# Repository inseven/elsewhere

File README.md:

# Elsewhere

Livestream picture frame

## Parts

| **Part**                                  | **Link**                                                     | Quantity | **Unit Price**            | **Price**   |
| ----------------------------------------- | ------------------------------------------------------------ | -------- | ------------------------- | ----------- |
| **Raspberry Pi Zero 2 W**                 | [Adafruit](https://www.adafruit.com/product/5291) | 1        | $15.00                   | $15.00     |
| **Pimoroni HDMI 10" IPS LCD Screen Kit**  | [Adafruit](https://www.adafruit.com/product/4337)            | 1        | $139.95                   | $139.95     |
| HDMI Ribbon Cable, 30 cm                  | [Adafruit](https://www.adafruit.com/product/3562)            | 1        | $2.75                     | $2.75       |
| HDMI Plug Adapter                         | [Adafruit](https://www.adafruit.com/product/3548)            | 1        | $6.50                     | $6.50       |
| Mini HDMI Plug Adapter                    | [Adafruit](https://www.adafruit.com/product/3552)            | 1        | $6.50                     | $6.50       |
| **ATXRaspi R3**                           | [LowPowerLab](https://lowpowerlab.com/shop/product/91)       | 1        | $17.95                    | $17.95      |
| Jumper Wire | [LowPowerLab](https://lowpowerlab.com/shop/product/154) | 4 | $0.74 ($2.95 for 4) | $2.95 |
| D-Ring Picture Hanger, M4                 |                                                              | 2        |                           |             |
| USB-C Panel Mount                         | [eBay](https://www.ebay.com/itm/143134180140)                | 1        | $6.29                     | $6.29       |
| USB-C to Micro USB Adapter                | [Amazon](https://www.amazon.com/gp/product/B07GH5KJH2/)      | 1        | $6.99                     | $6.99       |
| Micro USB Splitter Cable                  | [Amazon](https://www.amazon.com/gp/product/B017OPOG58/)      | 1        | $6.79                     | $6.79       |
| microSD Card, 32GB                        | [Amazon](https://www.amazon.com/SAMSUNG-Select-microSDXC-Adapter-MB-ME128HA/dp/B06XWN9Q99) | 1        | $7.99                     | $7.99       |
| Female to Female Dupont Wire, 30cm | [Amazon](https://www.amazon.com/dp/B07GD1W1VL) | 6 | $0.08 ($8.99 for 120) | $0.48 |
| M3 Standoff, 10mm                         | [McMaster-Carr](https://www.mcmaster.com/94868A166/)         | 8        | $1.24                     | $9.92       |
| 4-40 Socket Head Screw, Low-Profile, 1/4" | [McMaster-Carr](https://www.mcmaster.com/93615A110/)         | 2        | $1.55 (Pack of 10)        | $3.10       |
| M3 Socket Head Screw, Low-Profile, 12mm   | [McMaster-Carr](https://www.mcmaster.com/92855A313/)         | 8        | $0.11 (Pack of 25)        | $0.22       |
| M3 Socket Head Screw, Low-Profile, 6mm    | [McMaster-Carr](https://www.mcmaster.com/92855A307/)         | 8        | $0.30 (Pack of 25)        | $0.60       |
| M2.5 Socket Head Screw, 6mm               | [McMaster-Carr](https://www.mcmaster.com/91292A010/)         | 18      | $0.06 ($6.00 for 100) | $1.08    |
| M2.5 Socket Head Screw, 4mm | [McMaster-Carr](https://www.mcmaster.com/91292A015/) | 18 | $0.30 ($7.43 for 25) | $5.40 |
| M2.5 Socket Head Screw, 10mm | [McMaster-Carr](https://www.mcmaster.com/91292A014/) | 2 | $0.07 ($6.54 for 100) | $0.14 |
| M2.5 Nut | [McMaster-Carr](https://www.mcmaster.com/91828A113/) | 2 | $0.08 ($7.18 for 100) | $0.16 |
| M2.5 Washer, 0.5mm | [McMaster-Carr](https://www.mcmaster.com/98689A111/) | 6 | $0.03 ($2.57 for 100) | $0.18 |
| M4 Socket Head Screw, Low-Profile, Partially Threaded, 10mm | [McMaster-Carr](https://www.mcmaster.com/96970A111/) | 2 | $1.48 | $2.96 |
| M4 Washer, 0.8mm | [McMaster-Carr](https://www.mcmaster.com/93475A230/) | 2 | $0.04 ($3.14 for 100) | $0.08 |
| M4 Locknut | [McMaster-Carr](https://www.mcmaster.com/93625A150/) | 2 | $0.08 ($7.67 for 100) | $0.16 |
| M2.5 Standoff, 6mm                        | [Digi-Key](https://www.digikey.com/en/products/detail/970060154/732-12827-ND/9488531) | 18      | $0.34 ($16.95 for 50) | $6.12   |
| **Laser-Cut Parts** | [Ponoko](https://ponoko.com) |  |  | $118.99 |
| **Controller Board** | [Oshpark](https://oshpark.com/shared_projects/Cnb1DUgJ) | 1 | $3.49 ($10.45 for 3) | $3.49 |
| Micro SD to Micro SD Extension Cable, 25cm | [AliExpress](https://www.aliexpress.com/item/4001154489373.html) | 1 | $3.00 | $3.00 |
|                                           |                                                              |          |                           | **$375.74** |

## Wiring

## Software Installation

1. Install Raspberry Pi OS Lite (Bullseye).

2. Add the package repository to `/etc/apt/sources.list`:

   ```bash
   deb [trusted=yes] http://packages.inseven.co.uk/raspbian/ ./
   ```

3. Update the `dtoverlay` property in `/boot/config.txt` to:

   ```ini
   dtoverlay=vc4-fkms-v3d
   ```

   (See https://forums.raspberrypi.com/viewtopic.php?t=324835.)
   
4. Add `fbcon=map:2 disable_splash=1 ` to `/boot/cmdline.txt`.

   These changes are as follows:

   - `fbcon=map:2` – Redirects the console during boot to ensure it doesn't appear on the HDMI display.
   - `disable_splash=1` – Disable the boot splash screen.

5. Disable the Serial Port and SPI:

   ```bash
   sudo raspi-config
   ```

   - Disable Serial Port
     - Interface Options
     - Serial Port
     - Login Shell: No
     - Serial Port Hardware: No
   - Disable SPI
     - Interface Options
     - SPI
     - Enabled: No

6. Reboot:

   ```bash
   sudo reboot
   ```

7. Update and upgrade Raspbian, and install Elsewhere:

   ```bash
   sudo apt update
   sudo apt upgrade --yes
   sudo apt install elsewhere --yes
   ```

8. Assuming everything has gone to plan, Elsewhere should now be running.

#### Unattended Upgrades

1. Enable all [unattended upgrades](https://wiki.debian.org/UnattendedUpgrades) by uncommenting the following lines in `/etc/apt/apt.conf.d/50unattended-upgrades`:

   ```
   Unattended-Upgrade::Origins-Pattern {
           // ...
           "origin=Debian,codename=${distro_codename}-updates";
           "origin=Debian,codename=${distro_codename}-proposed-updates";
           // ..
   }
   ```

2. Reboot:

   ```bash
   sudo reboot
   ```

## Troubleshooting

### Device takes too long to shutdown and ATXRaspi doesn't cut power

- Re-enable the console by removing `fbcon=map:2` from `/boot/cmdline.txt`.
- Check the the shutdown logs; are any services taking a long time to stop?

### Tailscale doesn't takes too long to stop

Customise the Tailscale service to shorten the shutdown timeout:

- Override the service:

  ```bash
  sudo systemctl edit tailscaled.service
  ```

- Add the following section:

  ```
  [Service]
  TimeoutSec=5
  ```

## Builds

Elsewhere is an iterative project, meaning I've put together a number of prototypes along the way. The most recent one still has the 4:3 aspect ratio, and has been happily showing us views from the ISS for the last few months.

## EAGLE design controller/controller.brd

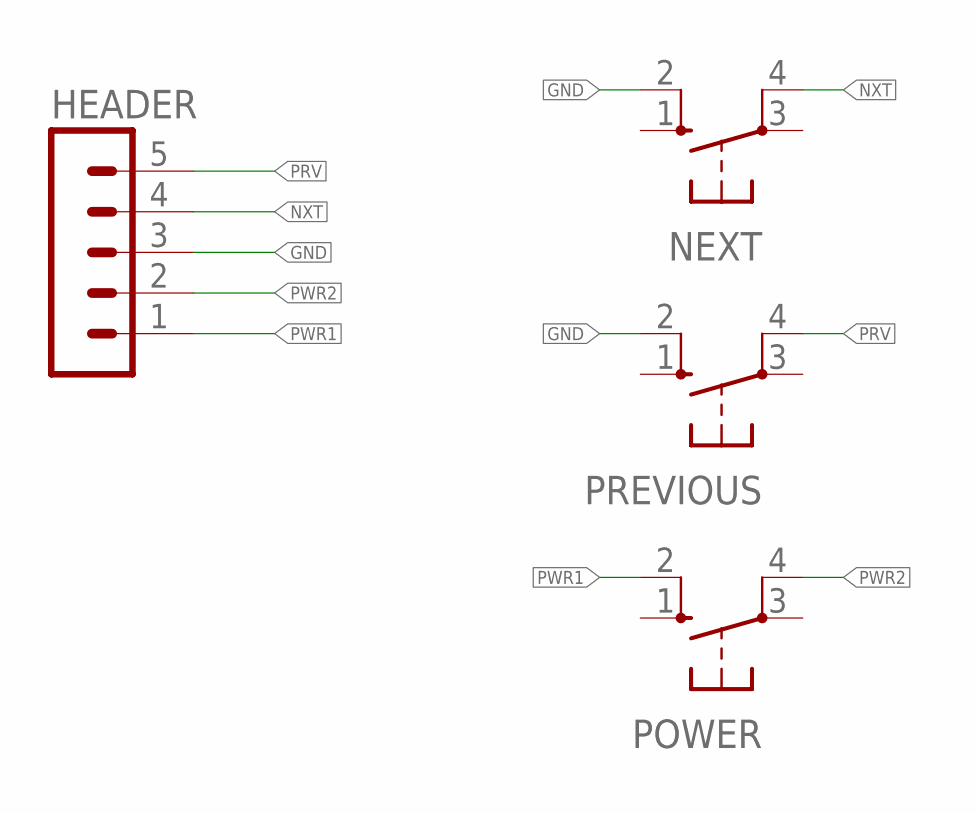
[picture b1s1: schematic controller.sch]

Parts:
HEADER: MA05-1
NEXT: 10-XX; B3F-10XX
POWER: 10-XX; B3F-10XX
PREVIOUS: 10-XX; B3F-10XX

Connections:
GND: HEADER.3, NEXT.2 (S1), PREVIOUS.2 (S1)
NXT: HEADER.4, NEXT.4 (P1)
PRV: HEADER.5, PREVIOUS.4 (P1)
PWR1: HEADER.1, POWER.2 (S1)
PWR2: HEADER.2, POWER.4 (P1)

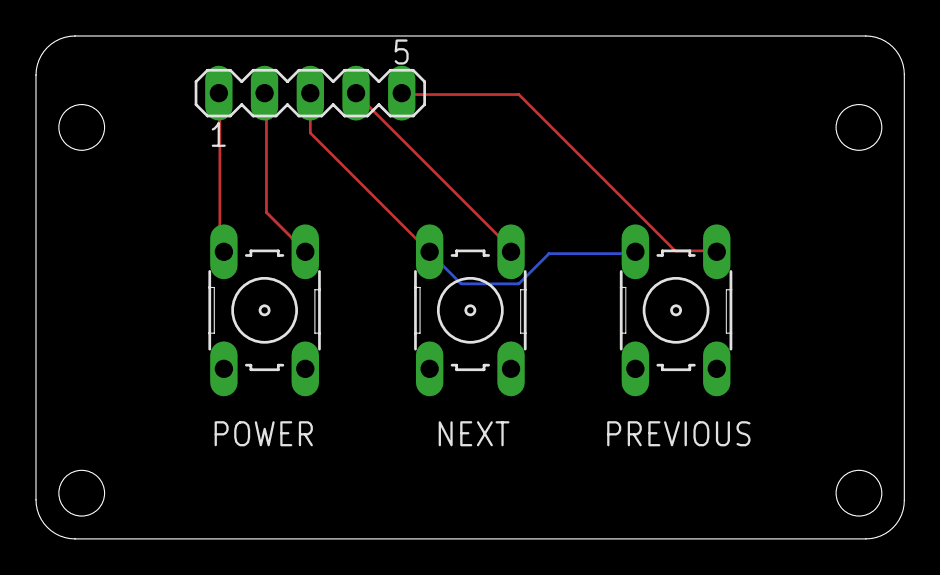
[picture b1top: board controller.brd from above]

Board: 2 copper layers, 48.2 x 27.9 mm, 4 parts (0 on the bottom side), 5 nets.

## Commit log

2018-09-07 Add template for fullscreen video.
2018-09-07 Render the template for each URL and display this.
2018-09-07 Prevent Chromium from restoring state.
2018-09-07 Use a temporary file.
2018-09-07 Black background.
2019-06-05 Add the model details.
2020-02-13 Add the manual for LP097QW1-SPC1.
2020-02-13 Move the schematics around, and add an export of just the front schematic.
2020-02-13 Add the SVG of the display schematics.
2020-04-29 Add prototype sketch.
2020-06-26 Update the elsewhere script to the new playback strategy.
2020-06-26 Update the name.
2020-06-26 Remove the unnecessary template.
2020-06-26 Support changing channels.
2020-06-27 Add a script for configuring elsewhere and update the readme accordingly.
2020-06-27 Experimental support for respawning the player if it crashes.
2020-06-28 Support changing channels with the threaded player.
2020-06-28 Sudo for reboot.
2020-06-30 Add CAD model.
2020-07-08 Replace the Tokyo stream.
2020-07-10 Update the CAD files.
2020-08-03 Support URL-based stream configuration.
2020-08-03 Update the setup script to configure simple logging.
2020-08-03 Ignore comments in the URL list.
2020-08-03 Ensure the process is launched using bash to allow us to use pipes.
2020-08-17 Support local files.
2020-08-17 Ignore urls.txt.
2020-08-18 Support skipping GPIO for control buttons and use the Pimoroni Inky pHAT as a display for stream titles.
2020-08-22 Add a preview.
2020-08-22 Add panel schematic
2020-08-22 Add a model
2020-08-22 More dependencies
2020-08-24 Add Raspberry Pi Zero schematic.
2020-08-25 Add the new manufacture exports.
2020-08-25 Rename placeholder screenshot.
2020-08-25 Move the prototype sketches into the models folder.
2020-08-25 Update the BOM
2020-08-25 Add the HDMI cable
2020-08-25 Update the render.
2020-08-25 Add a web server for controlling the device.
2020-08-25 Add a simple web app, and consolidate the player controls.
2020-08-29 Use the command line vlc client, and remove the eInk output for the time being.
2020-08-30 Adding the splash screen.
2020-08-30 Improving the layout of the controls slightly.
2020-08-30 Don't show the title when starting the stream.
2020-08-30 Add the Illustrator file for the splash screen.
2020-09-10 Add the first-cut service files.
2020-09-10 Lowercase buttons.
2020-12-30 Remove the legacy setup code.
2020-12-30 Titlecase.
2020-12-30 More titlecase.
2021-11-13 Add updated cut files with wider aspect ratio and many improvements
    - control mounts
    - improved hook mounting
    - larger USB-C cutout
    - SD card access
    - cleaner sides (fewer vents)
    - hidden joint between side panels
2021-11-16 Don't round the corners.
2021-11-17 Update the parts listing.
2021-11-17 Add the USB-C mounting screws.
2021-11-17 More screws, and total price.
2021-11-17 Add the ATXRaspi.
2021-11-17 Add screw.
2021-11-19 Add the microSD card to the BOM.
2021-11-24 Add the ATX-Raspi repository as a submodule.
2021-11-24 Add the ATXRaspi schematic from the website.
2021-11-26 Improve the setup documentation.
2021-11-26 Add PCB mounting standoffs and screws.
2021-11-27 Add an updated render.
2021-11-27 Brief comment about the most recent prototype.
2021-11-27 Gorup all the Adafruit components together.
2021-11-27 Cleaning up the multi-pack description.
2021-11-27 Add the v4 manufacture DXF files.
2021-11-27 Add an updated bottom side for the v3 build with a cutout for the power microswitch
2021-11-27 Add another stnadard part.
2021-11-27 Add the laser cut parts to the BoM.
2021-12-06 Add a simple script for showing the splash screen.
2021-12-06 Fix the path to the splash image.
2021-12-06 Add the Python requirements and a wrapper script to update them on first run
2021-12-06 Hard-code the path to streamlink.
2021-12-06 Add a package dependency file.
2021-12-06 Remove the legacy setup.py
2021-12-06 Remove the prototype eInk script.
2021-12-06 Add python-setuptools to the dependencies.
2021-12-06 Add the unattended updates packages.
2021-12-06 Some unattended updates setup.
2021-12-06 Remove legacy services.
2021-12-06 Update the README with further instructions for Bullseye.
2021-12-06 Fleshing out the UI a little.
2021-12-06 Updating the installation instructions and the install script.
2021-12-06 Add splash for shutting down.
2021-12-13 Add a small PCB with buttons for power and controlling the channels
2021-12-13 Link the controller PCB with Fusion.
2021-12-14 Add the latest manufacture files.
2021-12-18 Update the PCB mounting standoffs and screws.
2021-12-27 fix: Don't update the Python dependencies on every run
2021-12-27 fix: Support ATXRaspi power manaagement and add a splash screen
2021-12-27 fix: Use title case for the application name in the web frontend
2021-12-27 fix: Use Inter as the splash screen font
2021-12-27 chore: Remove the legacy Illustrator splash screens
2021-12-27 refactor: Move the splash service into the 'splash' directory
2021-12-27 fix: Don't use cron for running Elsewhere
2021-12-27 feat: Add a service for running the main Elsewhere script
2021-12-27 feat: Add the ATXRaspi monitor
2021-12-27 chore: Add a license to atx-monitor.py
2021-12-27 fix: Update the install script
2021-12-27 ci: Add empty GitHub Actions build
2021-12-27 ci: Correct the whitespace in the workflow (thanks Emacs)
2021-12-27 ci: Correct the target runner
2021-12-27 ci: Call the build script
2021-12-27 ci: Use a relative path to the build script
2021-12-27 ci: Build a dummy package
2021-12-27 feat: Install the splash screen service using the new debian package
2021-12-27 feat: Install the elsewhere service using the debian package
2021-12-27 fix: Remove the legacy package install step from `install.sh`
2021-12-27 ci: Archive the Debian package
2021-12-27 feat: Move the ATXRaspi monitor into the debian package
2021-12-27 feat: Move the elsewhere script into the debian package
2021-12-27 refactor: Remove the `install` command from atx-monitor
2021-12-27 ci: Add changes as a submodule
2021-12-27 docs: Add a build status badge
2021-12-27 fix: Include the Python dependencies in the debian package
2021-12-27 refactor: Move `requirements.txt` into the package directory
2021-12-27 fix: Python dependencies no longer need to be installed separately
2021-12-27 refactor: Move `install.sh` into the `scripts` directory
2021-12-27 feat: Add the version number to the splash screen
2021-12-27 fix: Show the version number in smaller font on the spash screen
2021-12-27 refactor: Move the build script into the scripts directory
2021-12-27 docs: Add a top-level license
2021-12-28 feat: Auto-generate version numbers using the `changes` script
2021-12-28 ci: Version number generation requires a full checkout
2021-12-28 ci: Correct the YAML whitespace (thanks Emacs)
2021-12-28 ci: Clear the Python dependencies on each re-install
2021-12-28 ci: Include the version number in the debian package filename
2021-12-28 ci: Rename the artifacts to `build`
2021-12-28 ci: Add an optional install step to the build script
2021-12-28 ci: Automatically create GitHub releases
2021-12-28 ci: Fix Emacs whitespace YAML errors
2021-12-28 fix: Update the package description
2021-12-29 fix: Set the Debian package build number
2021-12-29 fix: Only show the version number during startup
2021-12-30 feat: Generate a splash screen for use when restarting
2021-12-30 ci: Automatically update the package repository on main builds
2021-12-30 ci: Test package rebuild triggers
2021-12-30 fix: Artificially generated empty update to check the build process
2021-12-31 feat: Sign the debian packages
2021-12-31 ci: Remove control characters from the build workflow
2021-12-31 ci: Ensure `~/.gnupg` exists
2021-12-31 ci: Don't attempt to cleanup the GPG keys before they've been added
2021-12-31 docs: Update the documentation to use the new debian package
2022-01-02 chore: Add copyright header to the source files
2022-01-04 feat: Show stream titles
2022-01-04 fix: Add a dependency on ImageMagick
2022-01-05 fix: Correct the title for the Shinjuku stream
2022-01-05 feat: Add Shibuya Crossing stream
2022-01-08 docs: Add some troubleshooting documentation
2022-01-16 Update for the Raspberry Pi Zero 2 W.
2022-01-16 Remove two now-unused components
2022-01-17 Update the total price to account for the previously removed items
2022-01-17 Add the Elsewhere controller board to the BoM
2022-01-17 Add the Micro SD extension cable to the BoM
2022-01-17 Add the v6 DXF files
2022-01-17 Add the M4 mounting hardware from McMaster-Carr
2022-01-17 Add the SD card mounting hardware and the wires to the BoM
2022-01-17 Add models.
2022-01-21 feat: Add Brownville stream
2022-03-24 docs: Add a photo showing the internal inter-board wiring
2022-07-19 docs: Update the project description
2022-07-19 docs: Correct the updated project description
2022-12-19 docs: Update the description
2023-01-23 ci: Update `changes` to address new Pipenv requirements
2023-01-23 Don't install the GitHub CLI as part of the build
2023-01-23 ci: Update `changes` to address new Pipenv requirements (#52)
2023-01-23 ci: Update checkout action
2023-01-23 ci: Update checkout action (#53)
2023-01-23 ci: Update upload-artifact action
2023-01-23 ci: Update upload-artifact action (#54)
2023-01-23 ci: Update repository-dispatch action
2023-01-23 ci: Update repository-dispatch action (#55)
2023-11-01 fix: Remove livestreams that are no longer available
2023-11-01 Force a rebuild
2023-11-01 fix: Remove livestreams that are no longer available (#56)
2024-01-13 ci: Reschedule daily builds to night in Hawaii
2024-01-13 ci: Reschedule daily builds to night in Hawaii (#57)
2025-02-01 ci: Update upload-aftifact
2025-02-01 ci: Update upload-artifact (#58)
